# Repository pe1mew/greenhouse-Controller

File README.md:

# Greenhouse Ventilation Controller

An embedded controller for automated ventilation management of a single greenhouse. The controller reads internal climate (temperature and humidity) and external weather (wind speed and direction), and opens or closes three motorised ventilation windows to keep the climate within the setpoints configured by the farmer. A 4×4 keypad and 16×2 LCD provide local operation; optional WiFi and a built-in web GUI allow remote monitoring and configuration.

## What it does

The controller automatically ventilates a greenhouse by opening and closing three motorized windows to keep temperature and humidity within set limits, while protecting the structure from wind. It runs locally, keeps a full record of what it does, and can update itself.

### Automatic climate control (its main job)
- Continuously measures inside temperature and humidity and outside wind speed and direction; readings are smoothed so brief gusts or blips don't cause needless window movement.
- Opens or closes the windows to hold temperature and humidity within target ranges, with **separate day and night targets** — day and night are worked out from the local sunrise and sunset.
- When ventilation and humidity goals pull in opposite directions, a configurable priority decides which wins; humidity control can also be switched off entirely.
- The three windows — two roof vents and one large side-wall vent — are controlled independently, each with its own timing so movements are smooth and not too frequent.
- The large side-wall vent can carry a **position sensor**. With it fitted, the controller opens that vent **as far as the demand requires**, to a measured position, instead of all the way open or closed (**Lineair**, the factory default since 2.13.0). Whenever the position cannot be trusted, it falls back to timed control on its own.

### Wind safety
- If average wind speed exceeds a set limit, or the wind comes from a direction marked as risky, the windows are forced closed to protect the greenhouse — overriding normal climate control.

### Operating modes and manual control
- Three modes: **automatic**, **manual** (the operator positions the windows), and **standby** (automatic control paused).
- An administrator can drive each window by hand from the unit; doing so automatically pauses automatic control for that session so hand-set positions aren't overwritten.

### Safety and reliability
- Detects a window that fails to reach its commanded position and faults in the sensors, and raises an alarm.
- With the position sensor fitted, every movement of the side-wall vent is checked: did it get where it was sent? The configured travel time is also compared against the measured one.
- Ventilation and safety functions are kept isolated from the networking functions, so a network problem can never interfere with climate control.
- The controller monitors its own health, restarts cleanly if it ever locks up, and keeps a diagnostic record of any crash for later analysis.

### Local operation
- A keypad and display on the controller show live status — climate, wind, window positions, mode, network, and time — on rotating screens.
- Settings and manual control are protected by a PIN, with two access levels: a limited **farmer** role and a full **administrator** role.
- A recovery button lets someone reset the PIN or all settings, or restart the unit, without special tools.

### Web interface
- A built-in web page lets an operator view live status and change settings from a phone or computer.

### Configuration
- All settings — day/night temperature and humidity targets, wind limits, per-window timings, smoothing windows, location, and so on — are stored on the unit and changeable from the keypad or the web interface. Every change is recorded together with who made it.
- Local sunrise and sunset and daylight saving are determined from the geographical location of the internet connection.

### Remote monitoring and record-keeping
- Connects to WiFi and keeps accurate time.
- Records a detailed log of readings and events (mode changes, alarms, restarts, setting changes) to a memory card, automatically managing storage space.
- Regularly reports its status to a remote dashboard for off-site monitoring, and uploads its log files there too.

### Automatic updates
- The software and web interface can be updated two ways: by uploading an update through the web page, or by the unit fetching updates from a central server on its own. It installs them inside a configurable apply window (02:00–04:00 by default) while nobody is logged in, with no site visit needed. Updates are verified before installation, and the unit rolls back to the previous version if an update fails to start.

## Features

- Automatic climate control based on temperature and relative humidity setpoints (day / night)
- Two ventilation laws behind one host-tested contract ([`design/ventModelContract.md`](design/ventModelContract.md), implemented in `drivers/ventModel`):
  - **stepped**, the three-step strategy M1 → M1+M2 → M1+M2+M3, with hysteresis and sliding-average smoothing;
  - **graded**, which drives M3 to a proportional opening when its position sensor is fitted.
  - Both at **v2** since 2.15.0: humidity never closes a window against heat, and may open M1 on its own only above the crop's minimum temperature + 2 °C, if the operator allows it. The law in force, with its version, is in the SD log and in `/api/status` (`windows.law`).
- Optional **M3 window-position sensor**: a wire encoder on the RS485 bus (Modbus address 40) that also reports M3's end-of-travel sensors. It provides position control with automatic fallback to timed control, a verdict on every drive, and a travel-time check
- Wind safety override: all windows close automatically when wind speed exceeds a configurable threshold or wind direction lies in an excluded zone
- Motor alarm handling: immediate stop on Hotraco RRK-3 alarm output, with 60 s guard + automatic CLOSE_ALL re-calibration on clearance
- Three independent motorised window channels (M1 south roof, M2 north roof, M3 north wall)
- Modbus RTU / RS485 sensors: Seeed SenseCAP S200 (wind speed + direction), FG6485A (T/RH), and the optional M3 wire encoder
- Local user interface: 4×4 membrane keypad and 16×2 LCD with RGB status backlight (blue = OK, red = critical)
- PIN-based access control with two roles — Farmer (4-digit PIN) and Admin (8-digit PIN), salted-SHA-256 hashed
- Battery-backed DS1307 RTC for accurate timestamping; NTP sync when WiFi is available
- Event logging to SD card in CSV format — climate readings, relay actions, a config-change audit trail, and system events — parseable with the supplied `logparser`
- Built-in web GUI (HTML/JS served from LittleFS) with WebSocket live status, REST API, and push-OTA firmware/web-asset updates
- Remote OTA (ROTA): optional autonomous internet-pull updates — the controller authenticates to a configured server (per-unit HMAC, pinned server certificate), verifies each release against its manifest (SHA-256 + size) before flashing, and installs during a night window with anti-downgrade protection
- Status LEDs: RGB (system status), heartbeat (firmware alive)

## Hardware

| Component | Details |
|-----------|---------|
| Microcontroller | WEMOS LOLIN S3 (ESP32-S3, dual-core 240 MHz, 16 MB flash, 8 MB PSRAM) |
| Wind sensor | Seeed SenseCAP S200 — ultrasonic, Modbus RS485, 0–60 m/s |
| T/RH sensor | FG6485A — Modbus RS485, 9–36 VDC |
| Window position sensor (optional, M3) | Wire encoder with a CH32V003 Modbus RS485 interface board (address 40, 24 V passive PoE); its own repository, `wire-encoder-modbus-interface` |
| RS485 transceiver | MAX485 (TTL ↔ RS485 conversion) |
| Motor relay box | Hotraco RRK-3 — three-channel, 24 V potential-free OPEN/CLOSE control + alarm output |
| Display | LCD1602 I2C (AiP31068L bridge, address 0x3E), 16×2 characters with PCA9633 RGB backlight |
| Keypad | 4×4 membrane matrix keypad |
| RTC | DS1307 (I2C, CR2032 backup, ±20 ppm) |
| SD card | SPI, FAT32 (max 32 GB) for log retention |
| Power supply | 230 VAC → 24 VDC + 24 V → 5 V buck converter |
| Enclosure | IP-rated polycarbonate, mounted in the greenhouse near the entrance |
| PCB design | KiCad EDA v8+ |

## Repository Structure

```
greenhouse-Controller/
│
├── README.md           ← this file
├── changelog.md        ← per-version firmware changes
├── license.md / LICENSE
├── contributing.md
├── code_of_conduct.md
│
├── .githooks/          ← pre-commit hook (enable once per clone: git config core.hooksPath .githooks)
├── firmware/           ← PlatformIO ESP32-S3 firmware
├── drivers/            ← Host-tested driver and control-law libraries
├── webUiMock/          ← Flask mock server for web GUI development
├── model/              ← Simulation, plant-model tuning, settings verification
├── log/                ← Logparser tool + example log files
├── test/               ← Integration tests against live hardware
├── bin/                ← Released firmware + web-asset binaries (per version)
├── hardware/           ← KiCad PCB design + fabrication outputs
├── design/             ← Functional & technical design documents
├── documentation/      ← Component datasheets, sensor & motor reference material
├── realisation/        ← Installation wiring guide
├── manual/             ← End-user manuals (boer + beheerder), Dutch, MD + PDF
├── memory/             ← Project knowledge: architecture, gotcha log (read before debugging)
├── finance/            ← Project budget and receipts
└── Archive/            ← Historical design iterations (read-only)
```

### Top-level directories — what is in each

| Directory | Contents | Start here |
|---|---|---|
| **`firmware/`** | PlatformIO project for the ESP32-S3 controller. Source in `src/`, web-asset files (HTML / JS / CSS served from LittleFS) in `data/`, configuration headers in `config/`. Host-side unit tests live with their drivers in `drivers/<name>/test/` (see the row below), not under `firmware/`. Edit in VSCode with the PlatformIO extension. | [`firmware/platformio.ini`](firmware/platformio.ini), [`firmware/src/README.md`](firmware/src/README.md) |
| **`drivers/`** | One PlatformIO project per library: the peripheral drivers (DS1307_RTC, FG6485A, LCD1602_I2C, gpio, i2c, keyPad, littleFS, modBus, nvs, s200, sdCard, windowPos) and **ventModel**, the ventilation control law. Each has its own host-side unit tests (`pio test -e native`) and is compiled into the firmware through a thin `firmware/components/<name>/` proxy. `relay_sequence_test/` is the exception: a standalone bench sketch. | [`drivers/driverDevelopmentPlan.md`](drivers/driverDevelopmentPlan.md), per-driver READMEs in `drivers/<name>/` |
| **`webUiMock/`** | Lightweight Flask development server that serves the web GUI from `firmware/data/` and emulates every REST + WebSocket endpoint of the real firmware. Iterate on HTML/CSS/JS without flashing the board. | [`webUiMock/README.md`](webUiMock/README.md) |
| **`model/`** | Python software model of the controller (`simulation.py`) plus tools for plant-model calibration and settings verification. Used to tune parameters and validate firmware changes before deploying. Includes the May 2026 oscillation investigation. | [`model/README.md`](model/README.md) |
| **`log/`** | The `logparser.py` script that converts controller log CSVs (NVS ring buffer or SD-card files) into human-readable text, plus an example raw log and parsed output. | [`log/README.md`](log/README.md), [`log/logparser.md`](log/logparser.md) |
| **`test/`** | Integration tests against a live device + sensor emulator (PyTest + REST). Test-plan documents (`firmwareIntegrationTestPlan.md`, `softwareTestPlan.md`, `testPlan.md`, `manualREST.md`) and per-test scripts/results. | [`test/firmwareIntegrationTestPlan.md`](test/firmwareIntegrationTestPlan.md), [`test/softwareTestPlan.md`](test/softwareTestPlan.md) |
| **`bin/`** | Released firmware binaries and web-asset bundles, grouped per version (`bin/<version>/greenhouse-controller-<version>.bin` + `web-assets-<version>.zip`). Includes the `build_release.ps1` PowerShell script that produces a release. | [`bin/README.md`](bin/README.md) |
| **`hardware/`** | KiCad project for the PCB (`GreenhouseControllerPCB/`), fabrication outputs (`fabrication/` — Gerbers, BOM, pick-and-place), Modbus RS485 cable junction design (`ModBusRS485CableJunction/`), and bench-test setup (`Testing/`). | [`hardware/GreenhouseControllerPCB/README.md`](hardware/GreenhouseControllerPCB/README.md), [`hardware/fabrication/README.md`](hardware/fabrication/README.md) |
| **`design/`** | Functional & technical design documents that drove the implementation: requirements, architecture, LCD GUI design, default-settings rationale, FreeRTOS task analysis, web-GUI mouseover specs, version-control discussions, etc. | [`design/functionalRequirementsSpecification.md`](design/functionalRequirementsSpecification.md), [`design/technicalSoftwareDesignSpecification.md`](design/technicalSoftwareDesignSpecification.md), [`design/defalutSettingsMotivation.md`](design/defalutSettingsMotivation.md) |
| **`documentation/`** | Reference material from third parties and component vendors: sensor datasheets (`Sensors/`), motor docs (`Motors/`), ventilation system reference (`VentilationSystem/`), and Dutch agronomy literature on greenhouse climate. | [`documentation/Sensors/sensors.md`](documentation/Sensors/sensors.md), [`documentation/regelingOverwegingen.md`](documentation/regelingOverwegingen.md) |
| **`realisation/`** | Field-installation guide: how to wire all external components (sensors, motor box, mains, network) to the PCB connectors. | [`realisation/installation.md`](realisation/installation.md) |
| **`manual/`** | End-user manuals in **Dutch**, both as Markdown source and as printable PDF: a Farmer manual for daily use, and a Beheerder (Admin) manual for installation, configuration, maintenance and diagnosis. | [`manual/boerHandleiding.md`](manual/boerHandleiding.md), [`manual/beheerderHandleiding.md`](manual/beheerderHandleiding.md) |
| **`memory/`** | Project knowledge kept beside the code: the FreeRTOS task graph and subsystem map (`architecture.md`), the long-form "before you start" notes, and the **gotcha log** — every surprise met so far, with root cause and fix, indexed by subsystem. Check it before debugging anything odd. | [`memory/MEMORY.md`](memory/MEMORY.md), [`memory/gotcha-log.md`](memory/gotcha-log.md) |
| **`finance/`** | Project budget and receipts. Internal-use material; not relevant for using or building the controller. | – |
| **`Archive/`** | Historical first-iteration design and simulation work, kept read-only as reference. | [`Archive/Iteration1/design.md`](Archive/Iteration1/design.md) |

## Windows

The greenhouse has three motorised ventilation windows, each driven by one channel of the Hotraco RRK-3 motor relay box.

| ID | Location | Motor run-time (open / close) | Opening area |
|----|----------|------------------------------|-------------|
| M1 | South roof slope (Dakbeluchting Zuid) | 21 s / 21 s | 8 m² |
| M2 | North roof slope (Dakbeluchting Noord) | 21 s / 21 s | 8 m² |
| M3 | North wall side window (Zijwandbeluchting) | 171 s / 171 s | 80 m² |

M1 and M2 have no position feedback. The controller tracks their position from the OPEN/CLOSE commands it issued and the configured travel times. After every power-cycle a CLOSE_ALL calibration runs automatically (~3 minutes) to re-establish a known position.

M3 can carry the optional position sensor (since 2.8.0). With it fitted and its reading trusted, M3 is driven to a measured opening: **Lineair**, available since 2.12.0 and the factory default since 2.13.0. Without it, M3 runs on its travel time like M1 and M2. The sensor's setup, calibration and checks are described in [`design/integrateWindowPositionSensor.md`](design/integrateWindowPositionSensor.md).

## End-User Documentation (Dutch)

The two end-user manuals in `manual/` are the primary handover documents for greenhouse owners and their technical caretakers. They are kept in lock-step with the firmware version.

| Audience | Markdown source | Printable PDF |
|---|---|---|
| **Farmer / kasgebruiker** (daily use) | [`manual/boerHandleiding.md`](manual/boerHandleiding.md) | [`manual/boerHandleiding_Final.pdf`](manual/boerHandleiding_Final.pdf) |
| **Technical Beheerder / installer** (setup, configuration, maintenance, diagnosis) | [`manual/beheerderHandleiding.md`](manual/beheerderHandleiding.md) | [`manual/beheerderHandleiding_Final.pdf`](manual/beheerderHandleiding_Final.pdf) |

PDFs are generated from the Markdown sources by [`manual/build_pdf.py`](manual/build_pdf.py) — run `python manual/build_pdf.py` from the repo root. Requires Python 3.10+, the `markdown` package, and Microsoft Edge.

## Developer Documentation

| Document | Description |
|----------|-------------|
| [Functional Requirements Specification](design/functionalRequirementsSpecification.md) | What the system must do — all functional and technical requirements |
| [Local UI — LCD / keypad](design/technicalSoftwareDesignSpecification.md) | Screen layouts, menu structure, FSM, user-interaction patterns — §5.5 of the software TSDS. *(The standalone `LCD_GUI_Design.md` was retired at 1.16.3; an unversioned `.docx` of the original remains in `design/` but is not tracked.)* |
| [Default settings motivation](design/defalutSettingsMotivation.md) | Why the firmware factory defaults are what they are |
| [Driver Development Plan](drivers/driverDevelopmentPlan.md) | Per-driver development roadmap and verification approach |
| [Firmware Implementation Results](Archive/firmwareImplementationResults.md) | Phased implementation results from the original build-out. *(Superseded — the companion `firmwareImplementationPlan.md` was retired once the phases completed; current work is tracked in `changelog.md` and GitHub issues.)* |
| [Software Test Plan](test/softwareTestPlan.md) + [Firmware Integration Test Plan](test/firmwareIntegrationTestPlan.md) | Test cases and verification matrix |
| [Model & Simulation README](model/README.md) | Plant-model calibration, settings verification workflow, oscillation example |
| [Logparser manual](log/logparser.md) | CSV log format reference and `logparser.py` usage |
| [Web UI Mock Server](webUiMock/README.md) | How to develop the web GUI without the device |
| [Installation Wiring Guide](realisation/installation.md) | Field wiring of sensors, motor box, mains and network |
| [Ventilation law contract](design/ventModelContract.md) | The interface every control law implements; the stepped and graded laws live in `drivers/ventModel` with host tests |
| [Window position sensor](design/integrateWindowPositionSensor.md) | The M3 wire encoder: geometry, calibration, the presence gate, per-drive verdicts, and the two control modes |
| [Status website contract](design/technical-spec-statusWebsite.md) | The status POST payload and the log upload the remote dashboard consumes (contract 2.0) |
| [ROTA release tool](bin/rota_release.md) | Publishing a release to the internet-pull OTA channels |
| [Remote OTA (ROTA) design](design/rota_tds.md) | Internet-pull OTA — server contract, mutual-auth security model, night-window apply (mainline since 2.2.x; the `rota` branch merged to `main` and closed 2026-07-17 — branch history is in the `[2.2.0]` section of [changelog.md](changelog.md)) |
| [Changelog](changelog.md) | Per-version firmware change log |

## Getting Started — Build & Flash the Firmware

### Prerequisites

- [Visual Studio Code](https://code.visualstudio.com/) with the [PlatformIO IDE extension](https://platformio.org/install/ide?install=vscode)
- Git
- A WEMOS LOLIN S3 board, or the assembled controller PCB

### Build and Flash

```bash
git clone https://github.com/pe1mew/greenhouse-Controller.git
cd greenhouse-Controller
```

1. Open the `firmware/` folder in VS Code (PlatformIO will detect `platformio.ini` automatically).
2. Connect the LOLIN S3 board via USB-C.
3. Click **Upload** in the PlatformIO toolbar (or run `pio run -t upload` from `firmware/`).
4. Open the **Serial Monitor** (115200 baud) to view startup diagnostics.
5. For the web assets, do **not** use PlatformIO's "Upload Filesystem Image" (`pio run -t uploadfs`). In this project it builds a SPIFFS image and writes it to the wrong bank, and the firmware mounts LittleFS. Upload the web-assets ZIP over the network instead, or follow the cable procedure in [`bin/README.md`](bin/README.md) §2 Path D.

> **A new unit needs a one-time first flash**: the coredump partition erased, and the bootloader written with `--flash_mode dio`. See [`bin/README.md`](bin/README.md) §2 Path D, then run the unit for more than 30 s before unplugging it.

### First-time configuration

After a fresh flash or factory reset, the Beheerder configures the controller via:
- **LCD keypad** for first-time PIN entry, WiFi AP activation and date/time setting,
- **web GUI** (over the WiFi AP, then over the home WiFi) for everything else.

The full installation procedure is in [`manual/beheerderHandleiding.md`](manual/beheerderHandleiding.md) §11 and §13.

### Flashing a pre-built release

Released firmware and web-asset bundles for every version are in `bin/<version>/`. See [`bin/README.md`](bin/README.md) for the upload procedure (esptool / web-OTA / PlatformIO).

## License

See [`license.md`](license.md) for full details.

**Software** (firmware and all code): Source-available, non-commercial. Free to use and modify for personal/non-commercial purposes; redistribution and commercial use are not permitted.

**Hardware design, documentation, and images**: Licensed under the Creative Commons Attribution-NonCommercial-NoDerivatives 4.0 International License.

<br />Hardware design, documentation, and images are licensed under a <a rel="license" href="https://creativecommons.org/licenses/by-nc-nd/4.0/">Creative Commons Attribution-NonCommercial-NoDerivatives 4.0 International License</a>.

## Disclaimer

This project is distributed in the hope that it will be useful, but WITHOUT ANY WARRANTY; without even the implied warranty of MERCHANTABILITY or FITNESS FOR A PARTICULAR PURPOSE.

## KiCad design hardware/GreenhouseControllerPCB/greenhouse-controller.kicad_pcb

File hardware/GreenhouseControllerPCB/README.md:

# hardware/pcb

This directory contains the **KiCad** PCB design files for the Greenhouse Ventilation Controller.

## Tool

| Item | Value |
|------|-------|
| Tool | KiCad EDA version 8 or later |
| Licence | KiCad is free and open-source (GPL) |

## Expected contents (to be added)

| File / folder | Description |
|---------------|-------------|
| `greenhouse-controller.kicad_pro` | KiCad project file |
| `greenhouse-controller.kicad_sch` | Schematic |
| `greenhouse-controller.kicad_pcb` | PCB layout |
| `sym-lib-table` | Project symbol library table |
| `fp-lib-table` | Project footprint library table |
| `libraries/` | Project-specific symbol and footprint libraries |

## Design references

- Target board dimensions and component placement are guided by the enclosure selected in TDS §4.10 (Multicomp Pro MC001110, 222 × 146 × 55 mm).
- GPIO and peripheral assignments are specified in TDS §4.11.
- Fabrication outputs (Gerbers, BOM, pick-and-place) are generated from this design and stored in [`../fabrication/`](../fabrication/).

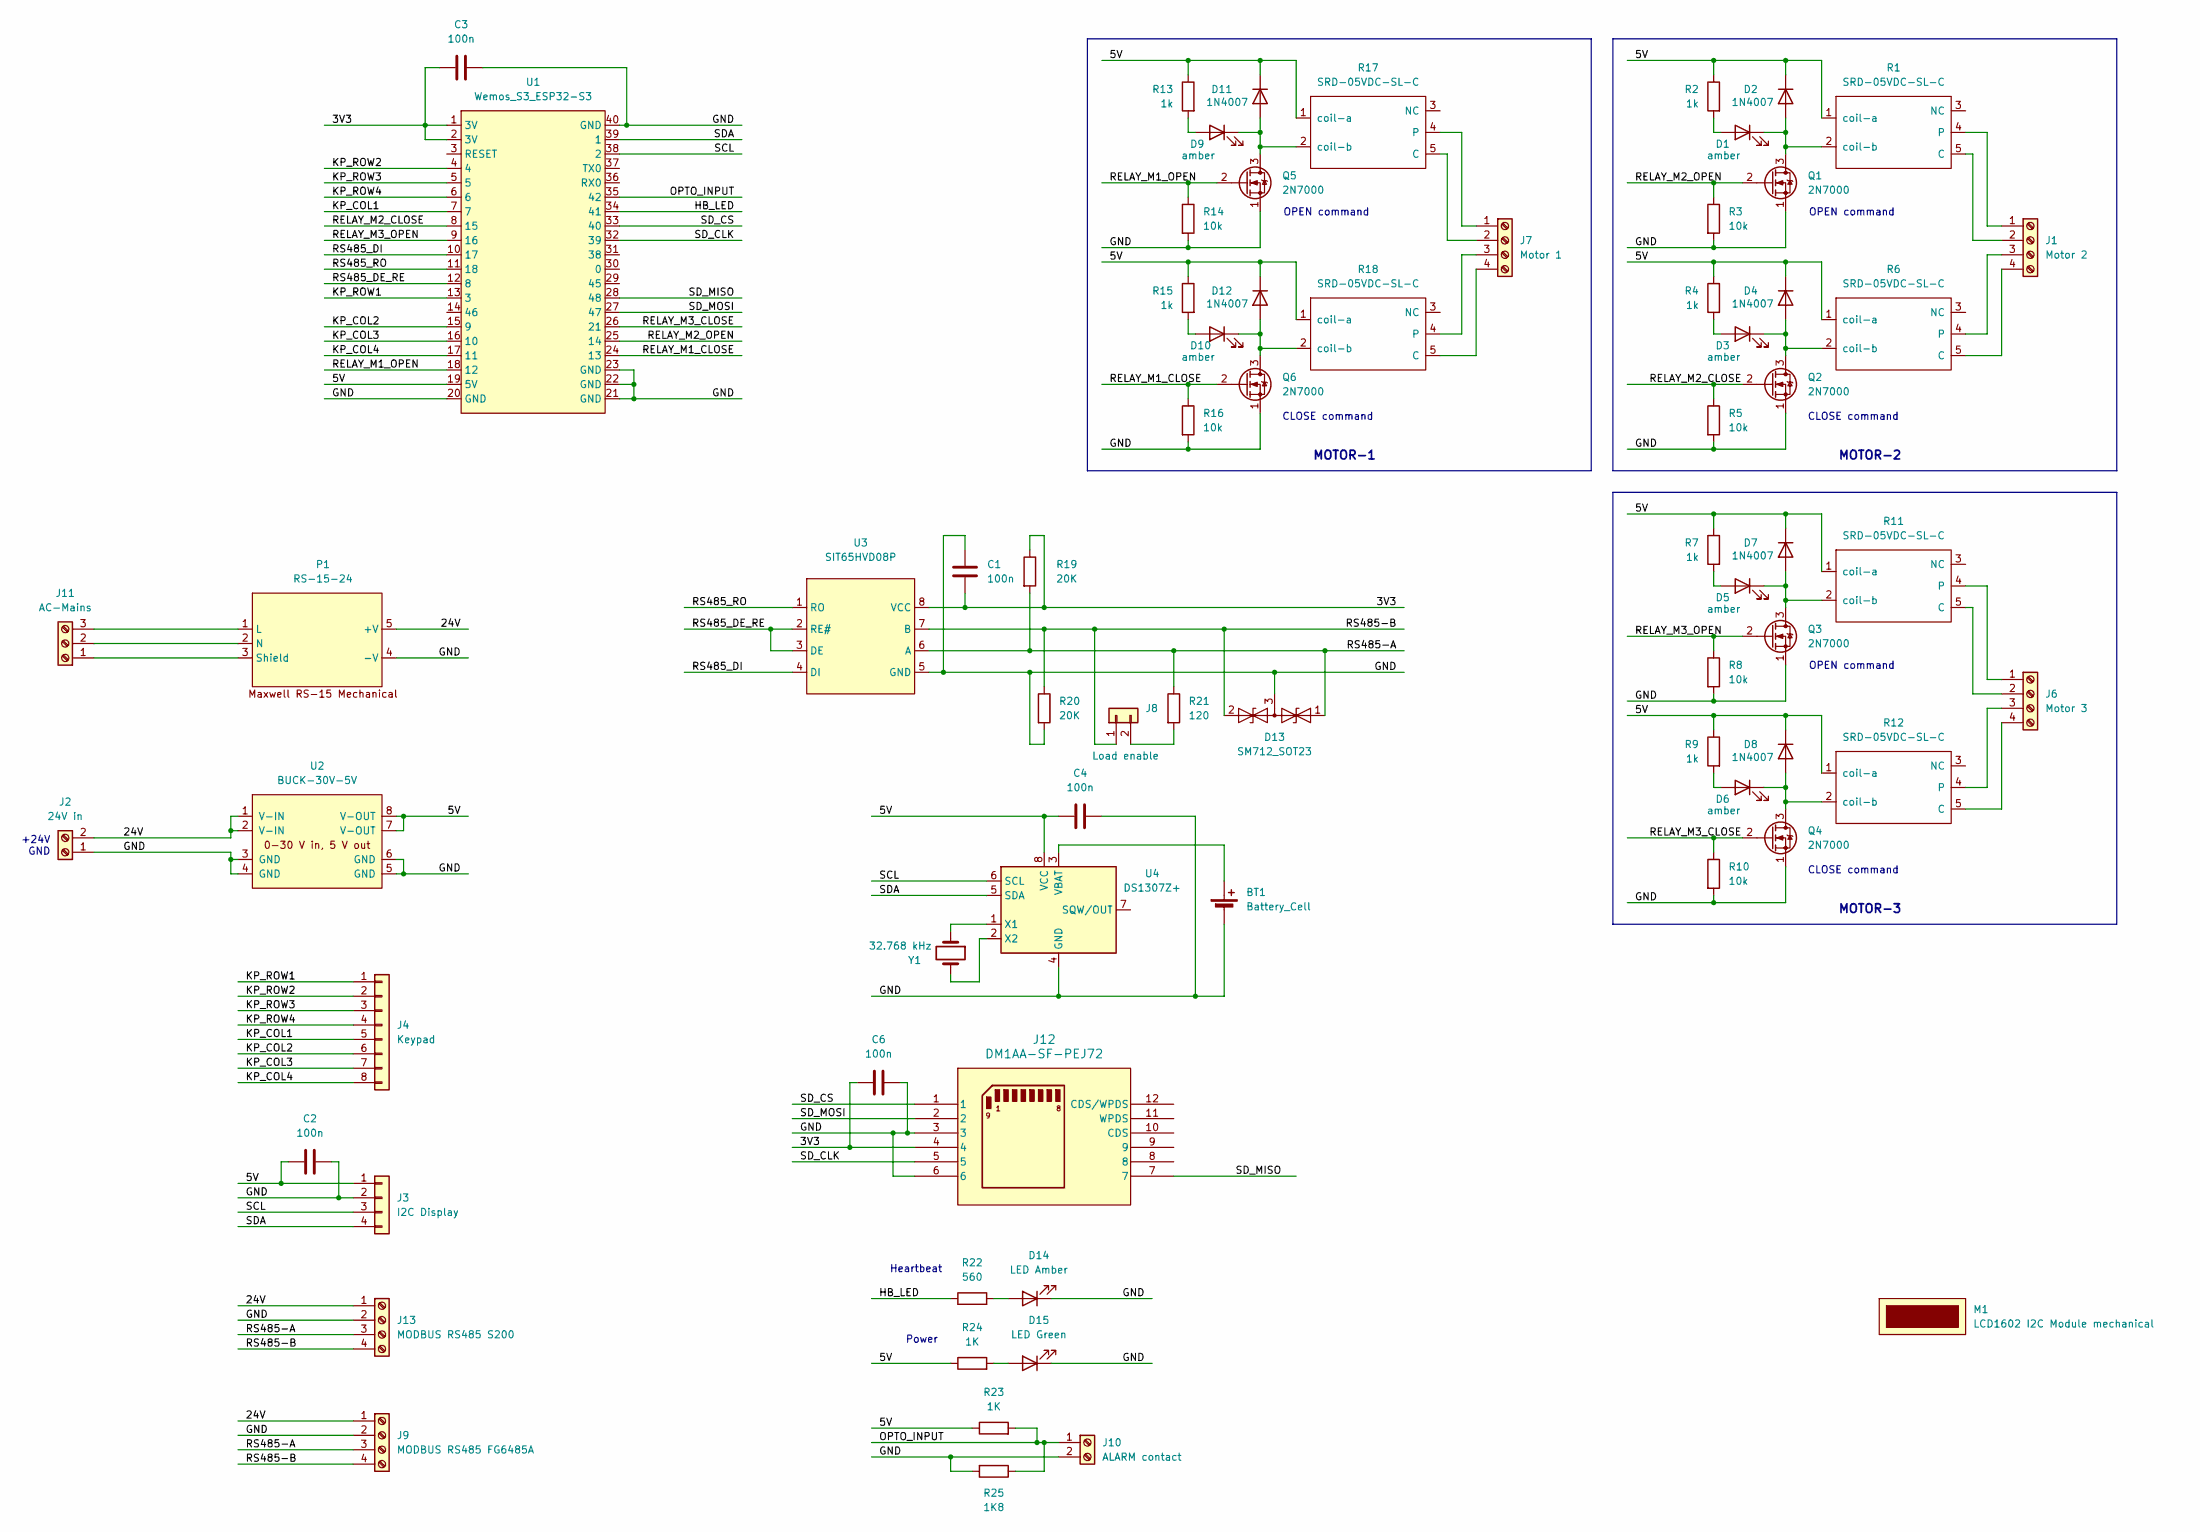
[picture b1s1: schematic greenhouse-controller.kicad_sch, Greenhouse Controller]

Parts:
BT1: Battery_Cell; BatteryHolder_MYOUNG_BS-07-A1BJ001_CR2032
C1, C2, C3, C4, C6: 100n; C_1206_3216Metric_Pad1.33x1.80mm_HandSolder
D1, D3, D5, D6, D9, D10: amber; LED_0805_2012Metric_Pad1.15x1.40mm_HandSolder
D2, D4, D7, D8, D11, D12: 1N4007; D_DO-41_SOD81_P10.16mm_Horizontal
D13: SM712_SOT23; SOT-23
D14: LED Amber; LED_0805_2012Metric_Pad1.15x1.40mm_HandSolder
D15: LED Green; LED_0805_2012Metric_Pad1.15x1.40mm_HandSolder
J1: Motor 2; TerminalBlock_Phoenix_MKDS-1,5-4_1x04_P5.00mm_Horizontal
J2: 24V in; TerminalBlock_Phoenix_MKDS-1,5-2_1x02_P5.00mm_Horizontal
J3: I2C Display; PinHeader_1x04_P2.54mm_Vertical
J4: Keypad; PinHeader_1x08_P2.54mm_Vertical
J6: Motor 3; TerminalBlock_Phoenix_MKDS-1,5-4_1x04_P5.00mm_Horizontal
J7: Motor 1; TerminalBlock_Phoenix_MKDS-1,5-4_1x04_P5.00mm_Horizontal
J8: Load enable; PinHeader_1x02_P2.54mm_Vertical
J9: MODBUS RS485 FG6485A; TerminalBlock_Phoenix_MKDS-1,5-4_1x04_P5.00mm_Horizontal
J10: ALARM contact; TerminalBlock_Phoenix_MKDS-1,5-2_1x02_P5.00mm_Horizontal
J11: AC-Mains; TerminalBlock_Phoenix_MKDS-1,5-3_1x03_P5.00mm_Horizontal
J12: DM1AA-SF-PEJ72; DM1AA-SF-PEJ72_HIR
J13: MODBUS RS485 S200; TerminalBlock_Phoenix_MKDS-1,5-4_1x04_P5.00mm_Horizontal
M1: LCD1602 I2C Module mechanical
P1: RS-15-24; Meanwell RS-15 Mechanical
Q1, Q2, Q3, Q4, Q5, Q6: 2N7000; TO-92_Inline
R1, R6, R11, R12, R17, R18: SRD-05VDC-SL-C
R2, R4, R7, R9, R13, R15: 1k; R_1206_3216Metric_Pad1.30x1.75mm_HandSolder
R3, R5, R8, R10, R14, R16: 10k; R_1206_3216Metric_Pad1.30x1.75mm_HandSolder
R19, R20: 20K; R_1206_3216Metric_Pad1.30x1.75mm_HandSolder
R21: 120; R_1206_3216Metric_Pad1.30x1.75mm_HandSolder
R22: 560; R_1206_3216Metric_Pad1.30x1.75mm_HandSolder
R23, R24: 1K; R_1206_3216Metric_Pad1.30x1.75mm_HandSolder
R25: 1K8; R_1206_3216Metric_Pad1.30x1.75mm_HandSolder
U1: Wemos_S3_ESP32-S3
U2: BUCK-30V-5V
U3: SIT65HVD08P; DIP-8_W7.62mm_LongPads
U4: DS1307Z+; SOIC-8_3.9x4.9mm_P1.27mm
Y1: 32.768 kHz; Crystal_DS26_D2.0mm_L6.0mm_Horizontal_1EP_style2

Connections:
/3V3: C1.2, C3.1, C6.1, J12.4, R19.1, U1.1 (3V), U1.2 (3V), U3.8 (VCC)
/5V: C2.1, C4.1, D2.1 (K), D4.1 (K), D7.1 (K), D8.1 (K), D11.1 (K), D12.1 (K), J3.1, R1.1 (coil-a), R2.1, R4.1, R6.1 (coil-a), R7.1, R9.1, R11.1 (coil-a), R12.1 (coil-a), R13.1, R15.1, R17.1 (coil-a), R18.1 (coil-a), R23.1, R24.1, U1.19 (5V), U2.7 (V-OUT), U2.8 (V-OUT), U4.8 (VCC)
/24V: J2.2, J9.1, J13.1, P1.5 (+V), U2.1 (V-IN), U2.2 (V-IN)
/GND: BT1.2 (-), C1.1, C2.2, C3.2, C4.2, C6.2, D13.3 (common), D14.1 (K), D15.1 (K), J2.1, J3.2, J9.2, J10.2, J12.3, J12.6, J13.2, P1.4 (-V), Q1.1 (S), Q2.1 (S), Q3.1 (S), Q4.1 (S), Q5.1 (S), Q6.1 (S), R3.2, R5.2, R8.2, R10.2, R14.2, R16.2, R20.2, R25.2, U1.20 (GND), U1.21 (GND), U1.22 (GND), U1.23 (GND), U1.40 (GND), U2.3 (GND), U2.4 (GND), U2.5 (GND), U2.6 (GND), U3.5 (GND), U4.4 (GND)
/HB_LED: R22.1, U1.34 (41)
/KP_COL1: J4.5, U1.7
/KP_COL2: J4.6, U1.15 (9)
/KP_COL3: J4.7, U1.16 (10)
/KP_COL4: J4.8, U1.17 (11)
/KP_ROW1: J4.1, U1.13 (3)
/KP_ROW2: J4.2, U1.4
/KP_ROW3: J4.3, U1.5
/KP_ROW4: J4.4, U1.6
/OPTO_INPUT: J10.1, R23.2, R25.1, U1.35 (42)
/RELAY_M1_CLOSE: Q6.2 (G), R16.1, U1.24 (13)
/RELAY_M1_OPEN: Q5.2 (G), R14.1, U1.18 (12)
/RELAY_M2_CLOSE: Q2.2 (G), R5.1, U1.8 (15)
/RELAY_M2_OPEN: Q1.2 (G), R3.1, U1.25 (14)
/RELAY_M3_CLOSE: Q4.2 (G), R10.1, U1.26 (21)
/RELAY_M3_OPEN: Q3.2 (G), R8.1, U1.9 (16)
/RS485-A: D13.1 (A1), J9.3, J13.3, R19.2, R21.1, U3.6 (A)
/RS485-B: D13.2 (A2), J8.1, J9.4, J13.4, R20.1, U3.7 (B)
/RS485_DE_RE: U1.12 (8), U3.2 (RE#), U3.3 (DE)
/RS485_DI: U1.10 (17), U3.4 (DI)
/RS485_RO: U1.11 (18), U3.1 (RO)
/SCL: J3.3, U1.38 (2), U4.6 (SCL)
/SDA: J3.4, U1.39 (1), U4.5 (SDA)
/SD_CLK: J12.5, U1.32 (39)
/SD_CS: J12.1, U1.33 (40)
/SD_MISO: J12.7, U1.28 (48)
/SD_MOSI: J12.2, U1.27 (47)
unnamed: BT1.1 (+), U4.3 (VBAT)
unnamed: D1.2 (A), R2.2
unnamed: D1.1 (K), D2.2 (A), Q1.3 (D), R1.2 (coil-b)
unnamed: D3.2 (A), R4.2
unnamed: D3.1 (K), D4.2 (A), Q2.3 (D), R6.2 (coil-b)
unnamed: D5.2 (A), R7.2
unnamed: D5.1 (K), D7.2 (A), Q3.3 (D), R11.2 (coil-b)
unnamed: D6.2 (A), R9.2
unnamed: D6.1 (K), D8.2 (A), Q4.3 (D), R12.2 (coil-b)
unnamed: D9.2 (A), R13.2
unnamed: D10.2 (A), R15.2
unnamed: D10.1 (K), D12.2 (A), Q6.3 (D), R18.2 (coil-b)
unnamed: D9.1 (K), D11.2 (A), Q5.3 (D), R17.2 (coil-b)
unnamed: D14.2 (A), R22.2
unnamed: D15.2 (A), R24.2
unnamed: J1.1, R1.4
unnamed: J1.2, R1.5 (C)
unnamed: J1.3, R6.4
unnamed: J1.4, R6.5 (C)
unnamed: J6.1, R11.4
unnamed: J6.2, R11.5 (C)
unnamed: J6.3, R12.4
unnamed: J6.4, R12.5 (C)
unnamed: J7.1, R17.4
unnamed: J7.2, R17.5 (C)
unnamed: J7.3, R18.4
unnamed: J7.4, R18.5 (C)
unnamed: J8.2, R21.2
unnamed: J11.1, P1.3 (Shield)
unnamed: J11.2, P1.2 (N)
unnamed: J11.3, P1.1 (L)
unnamed: U4.1 (X1), Y1.1
unnamed: U4.2 (X2), Y1.2

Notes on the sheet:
CLOSE command
MOTOR-3
OPEN command
Power
MOTOR-1
MOTOR-2
+24V GND
Heartbeat

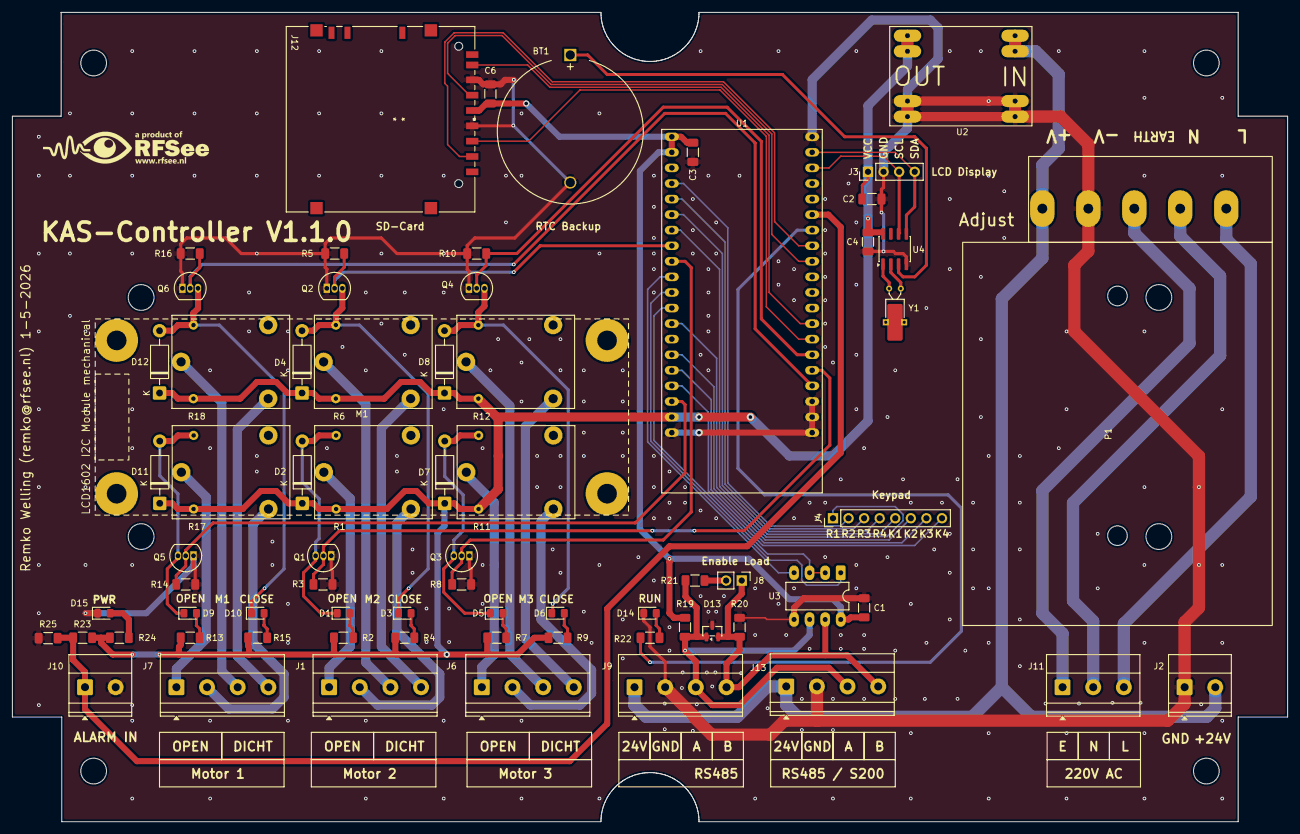
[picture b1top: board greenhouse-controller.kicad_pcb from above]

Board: 2 copper layers, 208.0 x 132.0 mm, 71 parts (0 on the bottom side), 64 nets.

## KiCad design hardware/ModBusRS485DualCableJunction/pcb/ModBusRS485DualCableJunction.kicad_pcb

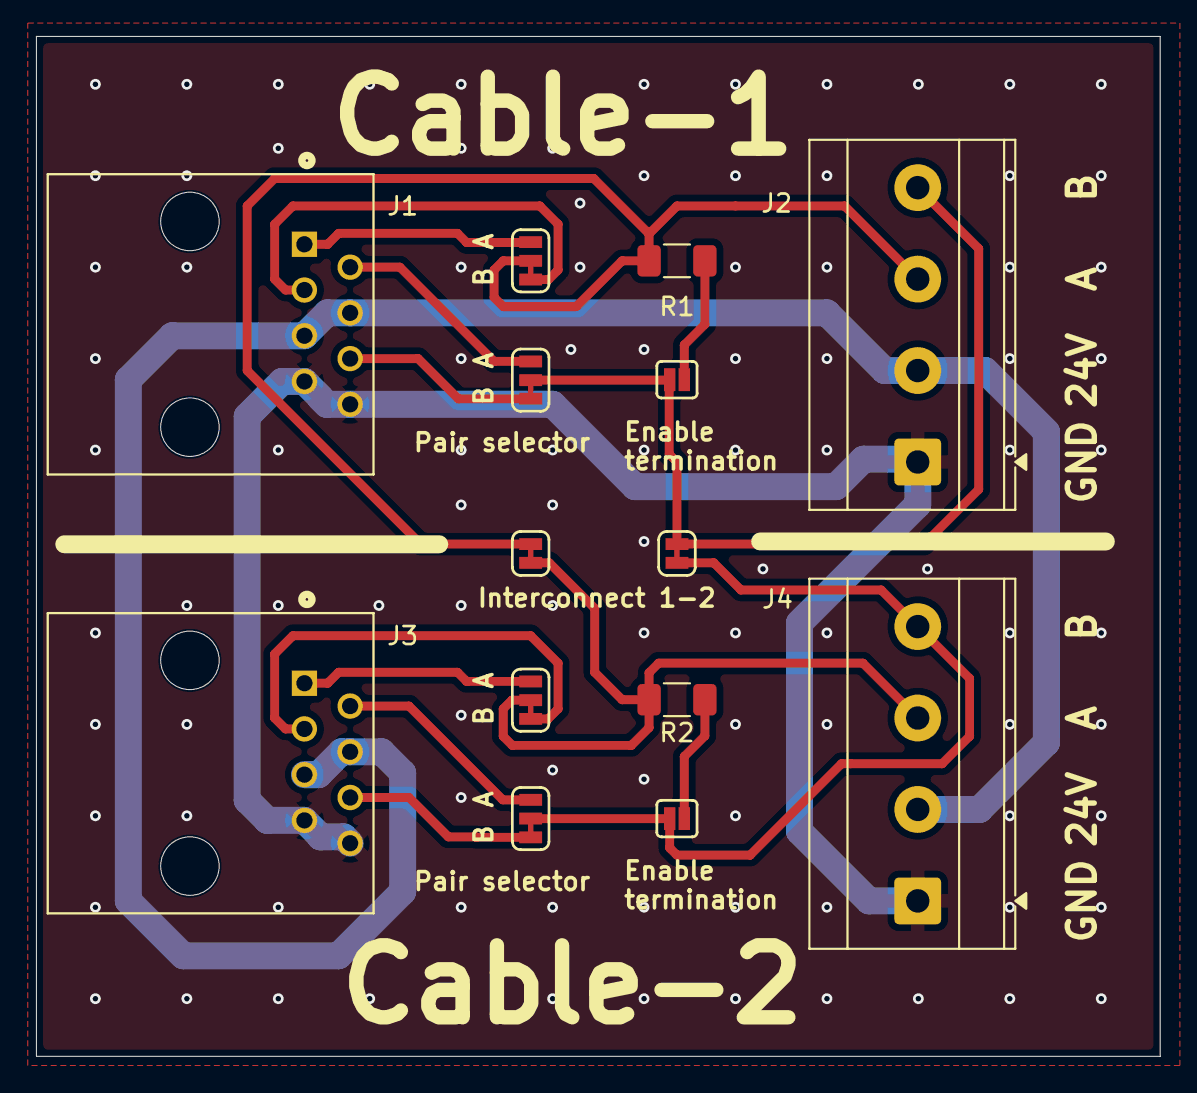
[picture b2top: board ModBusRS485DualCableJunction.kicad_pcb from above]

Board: 2 copper layers, 62.4 x 56.7 mm, 14 parts (0 on the bottom side), 16 nets.

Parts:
J1, J3: 215877-1; CONN_215877-1
J2, J4: Modbus Stub; TerminalBlock_Phoenix_MKDS-3-4-5.08_1x04_P5.08mm_Horizontal
JP1, JP2, JP4, JP5: Jumper_3_NC-1_Trace
JP7, JP8: Jumper_2_NC_Trace
JP9, JP10: Jumper_2_NO
R1, R2: 120; R_1206_3216Metric_Pad1.30x1.75mm_HandSolder

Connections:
/24V: J1.4 (3), J1.5 (6), J2.2, J3.4 (3), J3.5 (6), J4.2
/A: J2.3, JP1.2 (B), JP7.2 (B), R1.2
/Aa: J1.6 (5), JP2.1 (A)
/Ab: J1.2 (1), JP2.3 (C)
/B: J2.4, JP2.2 (B), JP8.2 (B), JP9.2 (B)
/Ba: J1.3 (4), JP1.1 (A)
/Bb: J1.1 (2), JP1.3 (C)
/GND: J1.7 (8), J1.8 (7), J2.1, J3.7 (8), J3.8 (7), J4.1
/_A: J4.3, JP5.2 (B), JP7.1 (A), R2.2
/_Aa: J3.6 (5), JP4.1 (A)
/_Ab: J3.2 (1), JP4.3 (C)
/_B: J4.4, JP4.2 (B), JP8.1 (A), JP10.2 (B)
/_Ba: J3.3 (4), JP5.1 (A)
/_Bb: J3.1 (2), JP5.3 (C)
unnamed: JP9.1 (A), R1.1
unnamed: JP10.1 (A), R2.1

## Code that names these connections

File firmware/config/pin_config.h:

/**
 * @file pin_config.h
 * @brief GPIO pin assignments — single authoritative source for all project GPIOs.
 *
 * Include this header wherever a project GPIO number is needed.
 * Do NOT hard-code GPIO numbers anywhere else in firmware or drivers.
 *
 * @par Reserved / inaccessible ESP32-S3 pins (must not be used)
 *   0, 19, 20, 22–25 (not on LOLIN S3 header), 26–37, 43, 44, 45, 46
 *
 * @author Greenhouse Controller project
 */

#pragma once

/* ---------------------------------------------------------------------------
 * Relay outputs (active-low relay driver inputs)
 * --------------------------------------------------------------------------- */

/** @brief Relay output — motor 1 OPEN direction. */
#define PIN_RELAY_M1_OPEN   12

/** @brief Relay output — motor 1 CLOSE direction. */
#define PIN_RELAY_M1_CLOSE  13

/** @brief Relay output — motor 2 OPEN direction. */
#define PIN_RELAY_M2_OPEN   14

/** @brief Relay output — motor 2 CLOSE direction. */
#define PIN_RELAY_M2_CLOSE  15

/** @brief Relay output — motor 3 OPEN direction. */
#define PIN_RELAY_M3_OPEN   16

/** @brief Relay output — motor 3 CLOSE direction. */
#define PIN_RELAY_M3_CLOSE  21

/* ---------------------------------------------------------------------------
 * Feedback input
 * --------------------------------------------------------------------------- */

/** @brief Digital input — opto-coupler feedback from RRK-3 motor controller. */
#define PIN_OPTO_INPUT      42

/* ---------------------------------------------------------------------------
 * Indicators
 * --------------------------------------------------------------------------- */

/** @brief Digital output — heartbeat / status LED (amber). */
#define PIN_HB_LED          41

/** @brief Digital output — on-board WS2812B RGB status LED (driven via RMT). */
#define PIN_RGB_LED         38

/* ---------------------------------------------------------------------------
 * RS-485 direction control
 * --------------------------------------------------------------------------- */

/** @brief Digital output — RS-485 transceiver DE/RE direction control. */
#define PIN_RS485_DE_RE      8

/** @brief UART1 TX — RS-485 transceiver DI (driver input). */
#define PIN_RS485_TX        17

/** @brief UART1 RX — RS-485 transceiver RO (receiver output). */
#define PIN_RS485_RX        18

/* ---------------------------------------------------------------------------
 * I2C bus (shared — LCD AiP31068L at 0x3E, RTC DS1307 at 0x68)
 * --------------------------------------------------------------------------- */

/** @brief I2C data line (SDA). */
#define PIN_I2C_SDA          1

/** @brief I2C clock line (SCL). */
#define PIN_I2C_SCL          2

/* ---------------------------------------------------------------------------
 * 4×4 membrane keypad (LIB-5)
 *
 * Row pins are driven LOW one at a time during scanning (OUTPUT, idle HIGH).
 * Column pins are read with internal pull-ups (INPUT_PULLUP); LOW = pressed.
 *
 * Key layout:
 *   Col:     1    2    3    4
 *   Row 1:  '1'  '2'  '3'  'A'
 *   Row 2:  '4'  '5'  '6'  'B'
 *   Row 3:  '7'  '8'  '9'  'C'
 *   Row 4:  '*'  '0'  '#'  'D'
 * --------------------------------------------------------------------------- */

/** @brief Keypad row 1 — OUTPUT, driven LOW to scan row 1. */
#define KP_ROW1              3

/** @brief Keypad row 2 — OUTPUT, driven LOW to scan row 2. */
#define KP_ROW2              4

/** @brief Keypad row 3 — OUTPUT, driven LOW to scan row 3. */
#define KP_ROW3              5

/** @brief Keypad row 4 — OUTPUT, driven LOW to scan row 4. */
#define KP_ROW4              6

/** @brief Keypad column 1 — INPUT_PULLUP; LOW when key in column 1 is pressed. */
#define KP_COL1              7

/** @brief Keypad column 2 — INPUT_PULLUP; LOW when key in column 2 is pressed. */
#define KP_COL2              9

/** @brief Keypad column 3 — INPUT_PULLUP; LOW when key in column 3 is pressed. */
#define KP_COL3             10

/** @brief Keypad column 4 — INPUT_PULLUP; LOW when key in column 4 is pressed. */
#define KP_COL4             11

/* ---------------------------------------------------------------------------
 * SPI SD card (LIB-8)
 * --------------------------------------------------------------------------- */

/** @brief SPI MOSI — SD card data out. */
#define PIN_SD_MOSI         47

/** @brief SPI MISO — SD card data in. */
#define PIN_SD_MISO         48

/** @brief SPI clock — SD card clock. */
#define PIN_SD_CLK          39

/** @brief SPI chip-select — SD card CS (active-low). */
#define PIN_SD_CS           40
